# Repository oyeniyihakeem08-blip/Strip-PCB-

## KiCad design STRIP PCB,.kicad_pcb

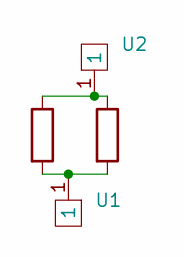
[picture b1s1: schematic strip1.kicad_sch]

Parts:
R1, R2: R; R_0805 editeded
U1, U2: Untitled

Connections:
unnamed: R1.1, R2.1, U2.1
unnamed: R1.2, R2.2, U1.1

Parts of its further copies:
R3, R4, R5, R6, R7, R8, R9, R10, R11, R12, R13, R14, R15, R16, R17, R18, R19, R20, R21, R22, R23, R24, R25, R26, R27, R28, R29, R30, R31, R32, R33, R34, R35, R36, R37, R38, R39, R40, R41, R42, R43, R44, R45, R46, R47, R48, R49, R50, R51, R52, R53, R54, R55, R56, R57, R58, R59, R60, R61, R62, R63, R64, R65, R66, R67, R68, R69, R70, R71, R72, R73, R74, R75, R76, R77, R78, R79, R80, R81, R82, R83, R84, R85, R86, R87, R88, R89, R90, R91, R92, R93, R94, R95, R96, R97, R98, R99, R100, R101, R102, R103, R104, R105, R106, R107, R108, R109, R110, R111, R112: R; R_0805 editeded
U3, U4, U5, U6, U7, U8, U9, U10, U11, U12, U13, U14, U15, U16, U17, U18, U19, U20, U21, U22, U23, U24, U25, U26, U27, U28, U29, U30, U31, U32, U33, U34, U35, U36, U37, U38, U39, U40, U41, U42, U43, U44, U45, U46, U47, U48, U49, U50, U51, U52, U53, U54, U55, U56, U57, U58, U59, U60, U61, U62, U63, U64, U65, U66, U67, U68, U69, U70, U71, U72, U73, U74, U75, U76, U77, U78, U79, U80, U81, U82, U83, U84, U85, U86, U87, U88, U89, U90, U91, U92, U93, U94, U95, U96, U97, U98, U99, U100, U101, U102, U103, U104, U105, U106, U107, U108, U109, U110, U111, U112: Untitled

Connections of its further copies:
unnamed: R3.1, R4.1, U4.1
unnamed: R3.2, R4.2, U3.1
unnamed: R5.1, R6.1, U6.1
unnamed: R5.2, R6.2, U5.1
unnamed: R7.1, R8.1, U8.1
unnamed: R7.2, R8.2, U7.1
unnamed: R9.1, R10.1, U10.1
unnamed: R9.2, R10.2, U9.1
unnamed: R11.1, R12.1, U12.1
unnamed: R11.2, R12.2, U11.1
unnamed: R13.1, R14.1, U14.1
unnamed: R13.2, R14.2, U13.1
unnamed: R15.1, R16.1, U16.1
unnamed: R15.2, R16.2, U15.1
unnamed: R17.1, R18.1, U18.1
unnamed: R17.2, R18.2, U17.1
unnamed: R19.1, R20.1, U20.1
unnamed: R19.2, R20.2, U19.1
unnamed: R21.1, R22.1, U22.1
unnamed: R21.2, R22.2, U21.1
unnamed: R23.1, R24.1, U24.1
unnamed: R23.2, R24.2, U23.1
unnamed: R25.1, R26.1, U26.1
unnamed: R25.2, R26.2, U25.1
unnamed: R27.1, R28.1, U28.1
unnamed: R27.2, R28.2, U27.1
unnamed: R29.1, R30.1, U30.1
unnamed: R29.2, R30.2, U29.1
unnamed: R31.1, R32.1, U32.1
unnamed: R31.2, R32.2, U31.1
unnamed: R33.1, R34.1, U34.1
unnamed: R33.2, R34.2, U33.1
unnamed: R35.1, R36.1, U36.1
unnamed: R35.2, R36.2, U35.1
unnamed: R37.1, R38.1, U38.1
unnamed: R37.2, R38.2, U37.1
unnamed: R39.1, R40.1, U40.1
unnamed: R39.2, R40.2, U39.1
unnamed: R41.1, R42.1, U42.1
unnamed: R41.2, R42.2, U41.1
unnamed: R43.1, R44.1, U44.1
unnamed: R43.2, R44.2, U43.1
unnamed: R45.1, R46.1, U46.1
unnamed: R45.2, R46.2, U45.1
unnamed: R47.1, R48.1, U48.1
unnamed: R47.2, R48.2, U47.1
unnamed: R49.1, R50.1, U50.1
unnamed: R49.2, R50.2, U49.1
unnamed: R51.1, R52.1, U52.1
unnamed: R51.2, R52.2, U51.1
unnamed: R53.1, R54.1, U54.1
unnamed: R53.2, R54.2, U53.1
unnamed: R55.1, R56.1, U56.1
unnamed: R55.2, R56.2, U55.1
unnamed: R57.1, R58.1, U58.1
unnamed: R57.2, R58.2, U57.1
unnamed: R59.1, R60.1, U60.1
unnamed: R59.2, R60.2, U59.1
unnamed: R61.1, R62.1, U62.1
unnamed: R61.2, R62.2, U61.1
unnamed: R63.1, R64.1, U64.1
unnamed: R63.2, R64.2, U63.1
unnamed: R65.1, R66.1, U66.1
unnamed: R65.2, R66.2, U65.1
unnamed: R67.1, R68.1, U68.1
unnamed: R67.2, R68.2, U67.1
unnamed: R69.1, R70.1, U70.1
unnamed: R69.2, R70.2, U69.1
unnamed: R71.1, R72.1, U72.1
unnamed: R71.2, R72.2, U71.1
unnamed: R73.1, R74.1, U74.1
unnamed: R73.2, R74.2, U73.1
unnamed: R75.1, R76.1, U76.1
unnamed: R75.2, R76.2, U75.1
unnamed: R77.1, R78.1, U78.1
unnamed: R77.2, R78.2, U77.1
unnamed: R79.1, R80.1, U80.1
unnamed: R79.2, R80.2, U79.1
unnamed: R81.1, R82.1, U82.1
unnamed: R81.2, R82.2, U81.1
unnamed: R83.1, R84.1, U84.1
unnamed: R83.2, R84.2, U83.1
unnamed: R85.1, R86.1, U86.1
unnamed: R85.2, R86.2, U85.1
unnamed: R87.1, R88.1, U88.1
unnamed: R87.2, R88.2, U87.1
unnamed: R89.1, R90.1, U90.1
unnamed: R89.2, R90.2, U89.1
unnamed: R91.1, R92.1, U92.1
unnamed: R91.2, R92.2, U91.1
unnamed: R93.1, R94.1, U94.1
unnamed: R93.2, R94.2, U93.1
unnamed: R95.1, R96.1, U96.1
unnamed: R95.2, R96.2, U95.1
unnamed: R97.1, R98.1, U98.1
unnamed: R97.2, R98.2, U97.1
unnamed: R99.1, R100.1, U100.1
unnamed: R99.2, R100.2, U99.1
unnamed: R101.1, R102.1, U102.1
unnamed: R101.2, R102.2, U101.1
unnamed: R103.1, R104.1, U104.1
unnamed: R103.2, R104.2, U103.1
unnamed: R105.1, R106.1, U106.1
unnamed: R105.2, R106.2, U105.1
unnamed: R107.1, R108.1, U108.1
unnamed: R107.2, R108.2, U107.1
unnamed: R109.1, R110.1, U110.1
unnamed: R109.2, R110.2, U109.1
unnamed: R111.1, R112.1, U112.1
unnamed: R111.2, R112.2, U111.1

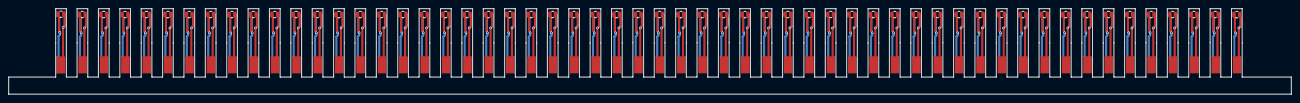
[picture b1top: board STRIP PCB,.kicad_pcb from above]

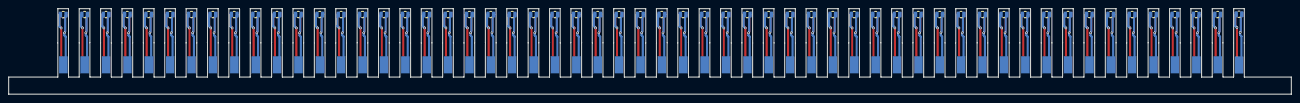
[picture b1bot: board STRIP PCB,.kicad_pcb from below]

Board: 2 copper layers, 300.0 x 20.0 mm, 224 parts (112 on the bottom side), 112 nets.

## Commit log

2025-12-12 initial upload
